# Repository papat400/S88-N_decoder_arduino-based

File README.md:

# English
## S88-N_decoder_arduino-based
Here is my version of the S88-N decoder. 
It uses an Arduino Nano and allows you to use it for block detection according to the Märklin principle or for potential-free electrical contacts. 16 inputs are available.

You can see typical connection examples in the **S88_bricolage.pdf** file.

* For block detection, optocouplers are used (see **IN_9** with **JP5 NOT CONNECTED**). Depending on the number of inputs used, you can choose the **LTV814, 824, or 844** models (1, 2 and 4 optocoupler per package, respectively).

* For electrical switch (ptoentiel-free) detection, you don't need optocouplers (see **S2**, with **JP6 connected**), except if you want to have a galvanic isolation (see **S1**). Without an optocoupler, it is necessary to solder a shunt by following the dotted lines on the PCB.

### Arduino:

The arduino sketch is in the **S88_UNO.zip** archive. It comes from Locoduino at https://www.locoduino.org/spip.php?article138

Inputs/outputs used by the S88 bus on the Nano:
- S88 Clock: pin = 2
- S88 PS: pin = 3
- Data Input coming from the previous Arduino in the S88 chain: pin = 0
- Data output to go to the next Arduino in the S88 chain or to the control unit: pin = 1
- **There is no RESET input**
- The S88 bus inputs are set to INPUT_PULLUP

Digital inputs used for contacts:
- Inputs 4 to 11 for the 8-input option
- Inputs 4 to 13 + Outputs 0 to 5 (configured as digital inputs) for the 16-input option
- The digital inputs are set to INPUT_PULLUP

For this sketch, you'll need **UNO_S88** library, available in the **UNO_S88.zip** archive.

### PCB:

There are two versions of the PCB: one with screw terminals (see **S88_Nano_16R0C_2Layers** files), the other with DuPont connectors (see **S88_Nano_16R0C_2Layers_DuPont** file). Each person can choose whichever they prefer.
The PCBs were designed using Eagle 9.6.2 free.

On the PCB, there is a jumper labeled **Data_In_To**. On the last S88 module (the one furthest from the control unit), you must place a shunt between the **central terminal** and **GND**. This is important.

The footprint of the RJ45 connector is shown on the file **dr-STW-SS-6488S-A-NF.pdf**.

---

# Français
## Décodeur S88-N basé sur Arduino
Voici ma version du décodeur S88-N.
Il utilise un Arduino Nano et permet, au choix, la détection de cantons selon le principe Märklin ou de contacts électriques libres de potentiel. 16 entrées sont disponibles.

Vous trouverez des exemples de branchement typiques dans le fichier **S88_bricolage.pdf**.

* Pour la détection de cantons, des optocoupleurs sont utilisés (voir **IN_9** avec **JP5 NON CONNECTÉ**). Selon le nombre d'entrées utilisées, vous pouvez choisir les modèles **LTV814, 824 ou 844** (1, 2 ou 4 optocoupleur par boîtier).

* Pour la détection de contact (libre de potentiel), les optocoupleurs ne sont pas nécessaires (voir **S2**, avec **JP6 connecté**), sauf si vous souhaitez une isolation galvanique (voir **S1**). Sans optocoupleur, il est nécessaire de souder un shunt en suivant les pointillés sur le PCB.

### Arduino :

Le programme Arduino se trouve dans l'archive **S88_UNO.zip**. Il provient de Locoduino : https://www.locoduino.org/spip.php?article138

Entrées/sorties utilisées par le bus S88 du Nano :
- Clock S88 : pin = 2
- PS S88 : pin = 3
- Data Input venant de l'Arduino précédent dans la chaîne S88 : pin = 0
- Data output pour aller vers l'Arduino suivant dans la chaîne S88 ou vers la centrale : pin = 1
- **Il n'y a pas d'entrée RESET**
- Les entrées Bus S88 sont en INPUT_PULLUP 
        
Entrées TOR (Tout Ou Rien) utilisées pour les contacts :
- Entrées 4 à 11 pour l'option 8 entrées
- Entrée 4 à 13 + Sorties 0 à 5 (paramétrées en entrées TOR) pour l'option 16 entrées
- Les entrées TOR sont en INPUT_PULLUP

Pour ce programme, vous aurez besoin de la bibliothèque **UNO_S88**, disponible dans l'archive **UNO_S88.zip**.

### PCB :

Il y a deux versions de PCB : un avec des borniers à vis (voir fichiers **S88_Nano_16R0C_2Layers**), l'autre avec des connecteurs DuPont (voir fichiers **S88_Nano_16R0C_2Layers_DuPont**). A chacun de choisir ce qu'il préfère.
Les PCB ont été dessinés avec Eagle 9.6.2 free.

Sur le PCB, on trouve un Jumper nommé **Data_In_To**. Sur le dernier module S88 (le plus éloigné de la centrale), il faut mettre un shunt entre **la borne centrale** et le **GND**. C'est important.

L'empreinte du connecteur RJ45 est présentée dans le fichier **dr-STW-SS-6488S-A-NF.pdf**.

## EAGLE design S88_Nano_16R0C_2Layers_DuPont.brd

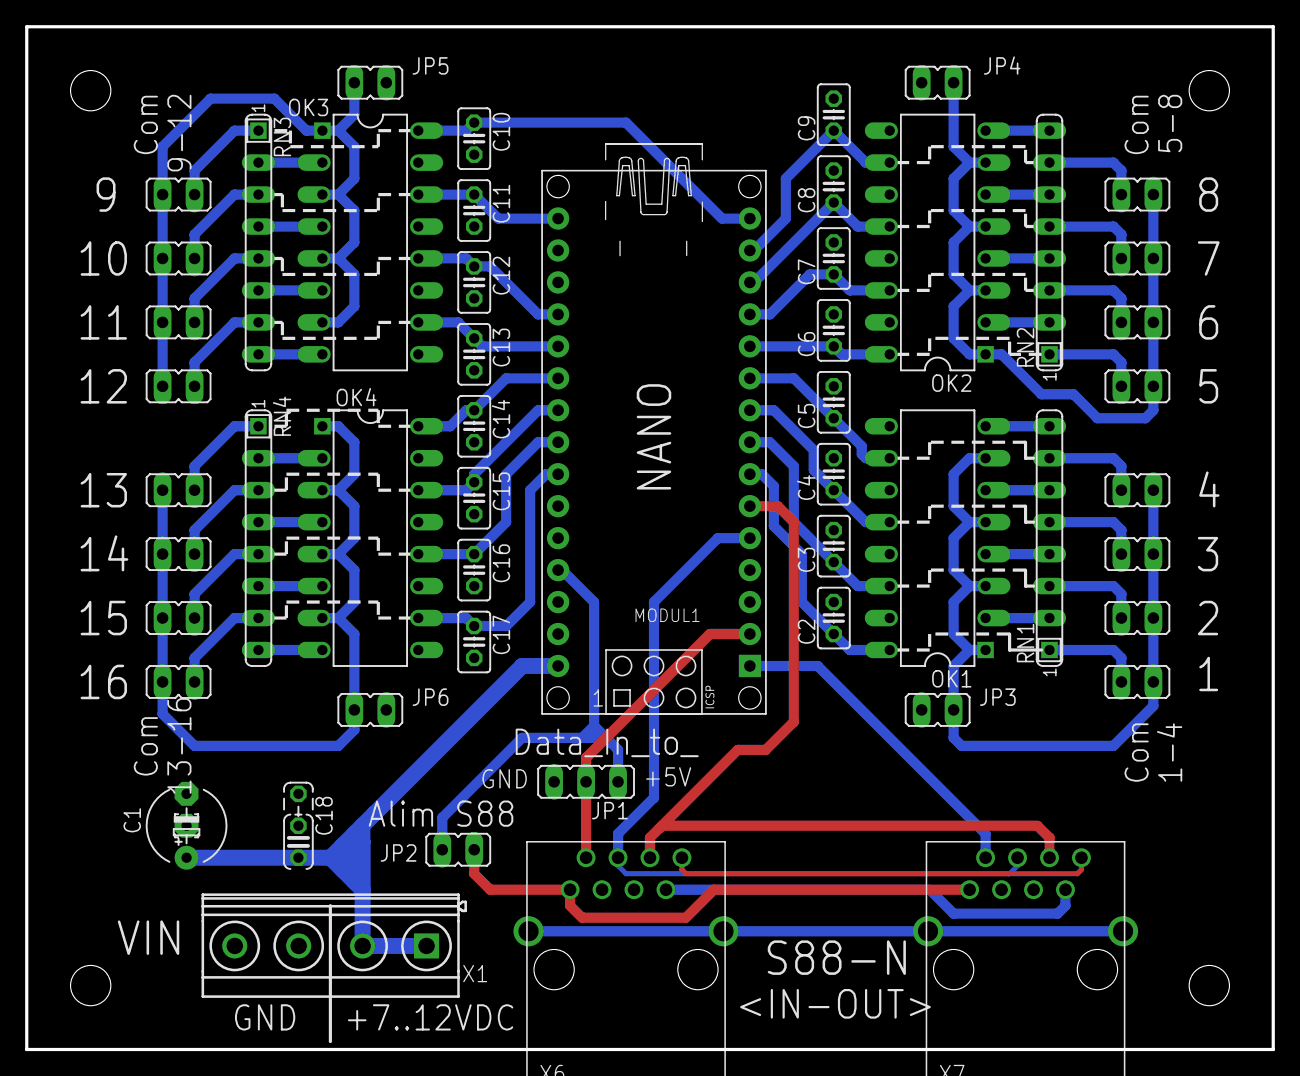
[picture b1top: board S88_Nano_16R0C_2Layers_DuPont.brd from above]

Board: 2 copper layers, 99.1 x 81.3 mm, 53 parts (0 on the bottom side), 63 nets.

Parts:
C1: 10µF; E5-6
C2, C3, C4, C5, C6, C7, C8, C9, C10, C11, C12, C13, C14, C15, C16, C17: 100n; C025-025X050
C18: 1nF; C025_050-024X070
JP1: Data_In_To_; JP2
JP2: Alim_S88; JP1
JP3: ComIn1; JP1
JP4: ComIn2; JP1
JP5: ComIn3; JP1
JP6: ComIn4; JP1
JP7, JP8, JP9, JP10, JP11, JP12, JP13, JP14, JP15, JP16, JP17, JP18, JP19, JP20, JP21, JP22: JP1
MODUL1: ARDUINO_NANO2
OK1, OK2, OK3, OK4: LTV844; DIL16
PAD1: 1,6/0,9
RN1, RN2, RN3, RN4: 10k; SIL8
X1: MKDSN1,5/4-5,08
X6, X7: RJ45-SHIELDED

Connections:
+5/S88: JP2.2, X6.1, X7.1
+5V: JP1.1, JP2.1, MODUL1.J2.4
A0: C12.1, MODUL1.J2.12, OK3.12
A1: C13.1, MODUL1.J2.11, OK3.10
A2: C14.1, MODUL1.J2.10, OK4.16
A3: C15.1, MODUL1.J2.9, OK4.14
A4: C16.1, MODUL1.J2.8, OK4.12
A5: C17.1, MODUL1.J2.7, OK4.10
CLK: MODUL1.J1.5, X6.4, X7.4
COM_IN_1_4: JP3.2, JP7.1, JP8.1, JP9.1, JP10.1, OK1.1, OK1.3, OK1.5, OK1.7
COM_IN_5_8: JP4.1, JP11.1, JP12.1, JP13.1, JP14.1, OK2.1, OK2.3, OK2.5, OK2.7
COM_IN_9_12: JP5.2, JP15.1, JP16.1, JP17.1, JP18.1, OK3.1, OK3.3, OK3.5, OK3.7
COM_IN_13_16: JP6.1, JP19.1, JP20.1, JP21.1, JP22.1, OK4.1, OK4.3, OK4.5, OK4.7
D4: C2.1, MODUL1.J1.7, OK1.16
D5: C3.1, MODUL1.J1.8, OK1.14
D6: C4.1, MODUL1.J1.9, OK1.12
D7: C5.1, MODUL1.J1.10, OK1.10
D8: C6.1, MODUL1.J1.11, OK2.16
D9: C7.1, MODUL1.J1.12, OK2.14
D10: C8.1, MODUL1.J1.13, OK2.12
D11: C9.1, MODUL1.J1.14, OK2.10
D12: C10.1, MODUL1.J1.15, OK3.16
D13: C11.1, MODUL1.J2.15, OK3.14
DATA_IN: JP1.2, MODUL1.J1.2, X6.2
DATA_OUT: MODUL1.J1.1, X7.2
GND: C1.-, C2.2, C3.2, C4.2, C5.2, C6.2, C7.2, C8.2, C9.2, C10.2, C11.2, C12.2, C13.2, C14.2, C15.2, C16.2, C17.2, C18.2, C18.3, JP1.3, JP3.1, JP4.2, JP5.1, JP6.2, MODUL1.J1.4, MODUL1.J2.2, OK1.9, OK1.11, OK1.13, OK1.15, OK2.9, OK2.11, OK2.13, OK2.15, OK3.9, OK3.11, OK3.13, OK3.15, OK4.9, OK4.11, OK4.13, OK4.15, PAD1.1, X1.3, X1.4, X6.3, X6.5, X7.3, X7.5
IN_1: OK1.2, RN1.2
IN_2: OK1.4, RN1.4
IN_3: OK1.6, RN1.6
IN_4: OK1.8, RN1.8
IN_5: OK2.2, RN2.2
IN_6: OK2.4, RN2.4
IN_7: OK2.6, RN2.6
IN_8: OK2.8, RN2.8
IN_9: OK3.2, RN3.2
IN_10: OK3.4, RN3.4
IN_11: OK3.6, RN3.6
IN_12: OK3.8, RN3.8
IN_13: OK4.2, RN4.2
IN_14: OK4.4, RN4.4
IN_15: OK4.6, RN4.6
IN_16: OK4.8, RN4.8
unnamed: JP7.2, RN1.1
unnamed: JP8.2, RN1.3
unnamed: JP9.2, RN1.5
unnamed: JP10.2, RN1.7
unnamed: JP11.2, RN2.1
unnamed: JP19.2, RN4.1
unnamed: JP14.2, RN2.7
unnamed: JP13.2, RN2.5
unnamed: JP18.2, RN3.7
unnamed: JP20.2, RN4.3
unnamed: JP12.2, RN2.3
unnamed: JP21.2, RN4.5
unnamed: JP22.2, RN4.7
unnamed: JP15.2, RN3.1
unnamed: JP16.2, RN3.3
unnamed: JP17.2, RN3.5
PS: MODUL1.J1.6, X6.6, X7.6
RAIL_DATA: X6.8, X7.8
RESET: X6.7, X7.7
SHIELD: X6.SHIELD, X6.SHIELD@1, X7.SHIELD, X7.SHIELD@1
VCC: C1.+, C18.1, MODUL1.J2.1, X1.1, X1.2

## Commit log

2025-10-29 Enhance README with detailed S88-N decoder info
    Expanded the README to include detailed information about the S88-N decoder's functionality, connection examples, and required components.
2025-10-29 Update README for PCB version descriptions
2025-10-29 Add RJ45 connector footprint details to README
    Added information about the RJ45 connector footprint.
2025-10-29 Update S88 bus pin assignments in README
    Clarified S88 bus pin assignments for Nano.
